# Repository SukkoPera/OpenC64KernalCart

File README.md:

# OpenC64KernalCart
OpenC64KernalCart is an Open Hardware Multi-KERNAL Cartridge for the Commodore 64.

### Summary
This project is derived from an old Turbo DOS V3 cartridge with the help of Jani. It allows replacing the [KERNAL (i.e.: operating system)](https://www.c64-wiki.com/wiki/Kernal) of a Commodore C64 computer with one that is stored on an external cartridge.

OpenC64KernalCart is designed to accept a 64 KB (512 Kilobit) (E)EPROM with a 27512-style pinout. Such chips can hold up to 8 KERNAL images, which can then be selected by jumpers. This makes it very easy to switch among KERNALs at will, without the need of opening the C64 every time. The recommended part is Winbond W27C512 (or W27E512, which is widely available, cheap and electrically erasable, which avoids the need for a clunky UV-eraser. This is the only part that was thoroughly tested. Other parts, even smaller in size, will probably work, but will require an ad-hoc configuration.

The only inconvenience is that you will need to open your C64 once, in order to connect a wire to CPU pin 28 (or wherever you can find the HIRAM signal, grab a multimeter and check for continuity here and there). You will need to connect this wire to the header that is provided on the cartridge for full KERNAL replacement. Note that the cartridge will also appear to work even when this wire is not connected, but that will not allow the external KERNAL to have access to the full RAM range of the C64, which will lead to incompatibilities.

Jani has published [a nice article](http://blog.worldofjani.com/?p=3736) on how we developed this cartridge and how it works in detail, so please refer to it for further information.

### Configuration
**IMPORTANT: ALWAYS TURN YOUR C64 OFF BEFORE MOVING THE CONFIGURATION JUMPERS.**
 
When flashing the contents, make sure that every file is exactly 8192 bytes long and just concatenate them. Then use the following table to set the jumper configuration for your image of choice:

| KERNAL Image # | A13 | A14 | A15 |
|----------------|-----|-----|-----|
| 1              |  L  |  L  |  L  |
| 2              |  H  |  L  |  L  |
| 3              |  L  |  H  |  L  |
| 4              |  H  |  H  |  L  |
| 5              |  L  |  L  |  H  |
| 6              |  H  |  L  |  H  |
| 7              |  L  |  H  |  H  |
| 8              |  H  |  H  |  H  |
 
### License
The OpenC64KernalCart documentation, including the design itself, is copyright &copy; SukkoPera 2019.

OpenC64KernalCart is Open Hardware licensed under the [CERN OHL v. 1.2](http://ohwr.org/cernohl).

You may redistribute and modify this documentation under the terms of the CERN OHL v.1.2. This documentation is distributed *as is* and WITHOUT ANY EXPRESS OR IMPLIED WARRANTIES whatsoever with respect to its functionality, operability or use, including, without limitation, any implied warranties OF MERCHANTABILITY, SATISFACTORY QUALITY, FITNESS FOR A PARTICULAR PURPOSE or infringement. We expressly disclaim any liability whatsoever for any direct, indirect, consequential, incidental or special damages, including, without limitation, lost revenues, lost profits, losses resulting from business interruption or loss of data, regardless of the form of action or legal theory under which the liability may be asserted, even if advised of the possibility or likelihood of such damages.

A copy of the full license is included in file [LICENSE.pdf](LICENSE.pdf), please refer to it for applicable conditions. In order to properly deal with its terms, please see file [LICENSE_HOWTO.pdf](LICENSE_HOWTO.pdf).

The contact points for information about manufactured Products (see section 4.2) are listed in file [PRODUCT.md](PRODUCT.md).

Any modifications made by Licensees (see section 3.4.b) shall be recorded in file [CHANGES.md](CHANGES.md).

The Documentation Location of the original project is https://github.com/SukkoPera/OpenC64KernalCart/.

### Support the Project
Since the project is open you are free to get the PCBs made by your preferred manufacturer, however in case you want to support the development, you can order them from PCBWay through this link:

You get my gratitude and cheap, professionally-made and good quality PCBs, I get some credit that will help with this and [other projects](https://www.pcbway.com/project/member/shareproject/?bmbid=41100). You won't even have to worry about the various PCB options, it's all pre-configured for you!

Also, if you still have to register to that site, [you can use this link](https://www.pcbway.com/setinvite.aspx?inviteid=41100) to get some bonus initial credit (and yield me some more).

Again, if you want to use another manufacturer, feel free to, don't feel obligated :). But then you can buy me a coffee if you want:

### Get Help
If you need help or have questions, you can join [the official Telegram group](https://t.me/joinchat/HUHdWBC9J9JnYIrvTYfZmg).

### Thanks
- Jani for involving me into this project.

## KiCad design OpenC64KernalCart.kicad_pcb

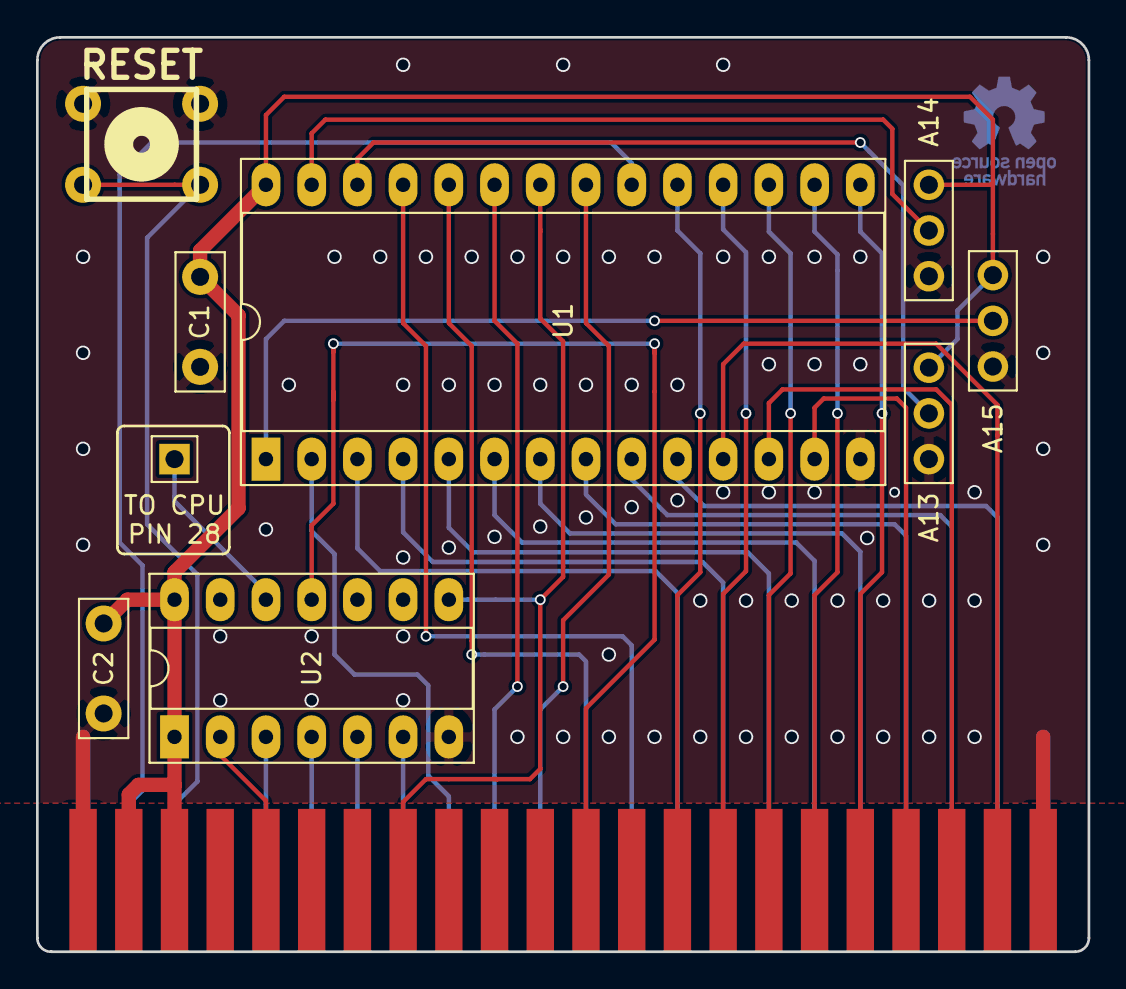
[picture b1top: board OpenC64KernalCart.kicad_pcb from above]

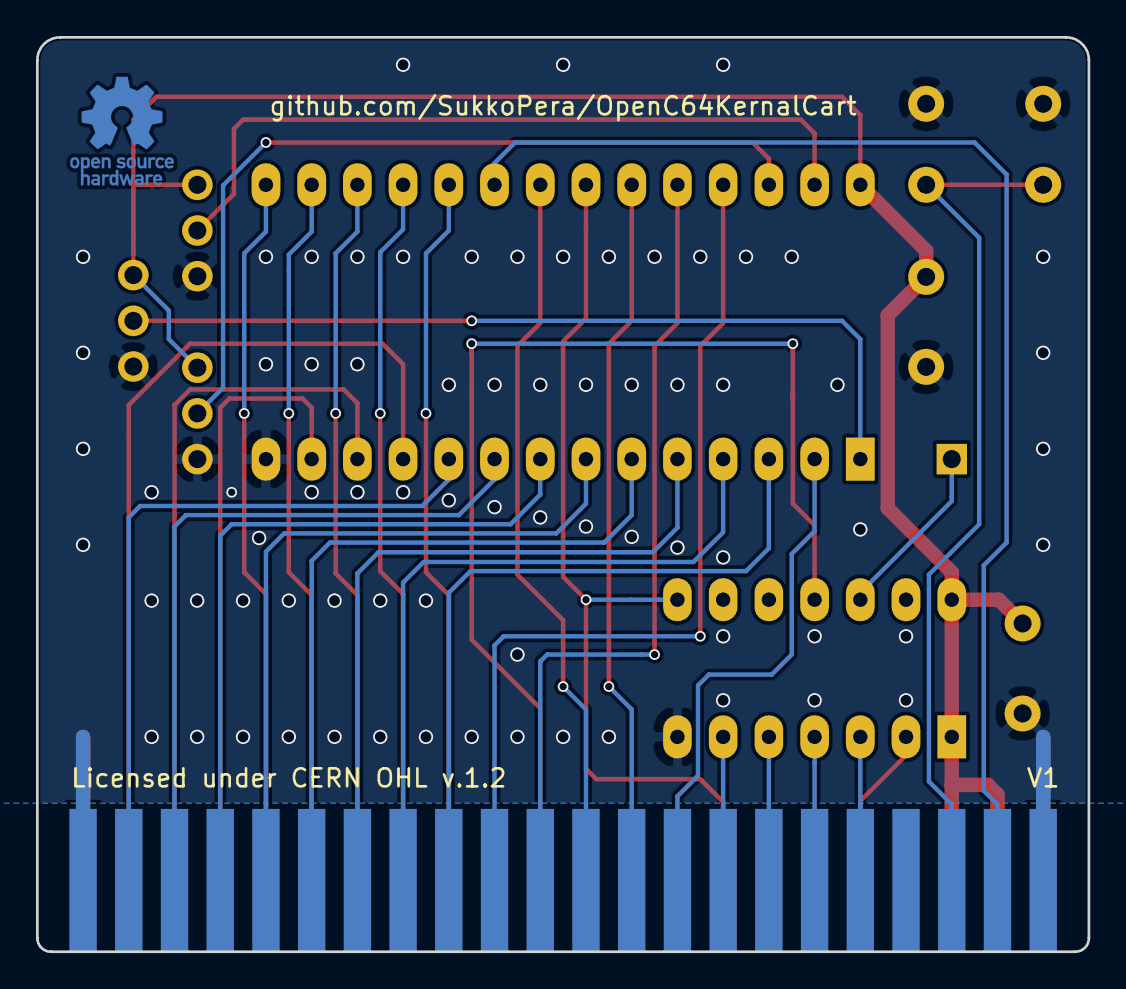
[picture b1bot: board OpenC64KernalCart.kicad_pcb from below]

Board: 2 copper layers, 58.4 x 50.8 mm, 13 parts (2 on the bottom side), 36 nets.

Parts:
C1, C2: 100n; C_Disc_D7.5mm_W2.5mm_P5.00mm
J1: C64-Exp-Port; C64-Cart
J2: CPU_WIRE; PinHeader_1x01_P2.54mm_Vertical
J97: TOP_TRACKS; top
J98: BOTTOM_TRACKS; bottom
J99: OSHW_LOGO; OSHW-Logo_5.7x6mm_Copper
SW2: RESET_SWITCH; PCB_PUSH
SW13: KERNEL_BANK_A13; Switch
SW14: KERNEL_BANK_A14; Switch
SW15: KERNEL_BANK_A15; Switch
U1: 27512; DIP-28_W15.24mm_Socket_LongPads
U2: 74LS30; DIP-14_W7.62mm_Socket_LongPads

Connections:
/a0: J1.Y, U1.10
/a1: J1.X, U1.9
/a2: J1.W, U1.8
/a3: J1.V, U1.7
/a4: J1.U, U1.6
/a5: J1.T, U1.5
/a6: J1.S, U1.4
/a7: J1.R, U1.3
/a8: J1.P, U1.25
/a9: J1.N, U1.24
/a10: J1.M, U1.21
/a11: J1.L, U1.23
/a12: J1.K, U1.2
/a13: J1.J, U2.6
/a13x: SW13.1, U1.26
/a14: J1.H, U2.5
/a14x: SW14.1, U1.27
/a15: J1.F, U2.4
/a15x: SW15.1, U1.1
/ba: J1.12, U2.11
/d0: J1.21, U1.11
/d1: J1.20, U1.12
/d2: J1.19, U1.13
/d3: J1.18, U1.15
/d4: J1.17, U1.16
/d5: J1.16, U1.17
/d6: J1.15, U1.18
/d7: J1.14, U1.19
/game: J1.8, U1.22, U2.8
/phi2: J1.E, U2.3
/reset: J1.C, SW2.1, SW2.2
/romh: J1.B, U1.20
/rw: J1.5, U2.2
/wire: J2.1, U2.12
GND: C1.2, C2.2, J1.1, J1.22, J1.A, J1.Z, SW2.3, SW2.4, SW13.3, SW14.3, SW15.3, U1.14, U2.7
VCC: C1.1, C2.1, J1.2, J1.3, SW13.2, SW14.2, SW15.2, U1.28, U2.1, U2.14

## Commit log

2019-05-20 Initial version, as close as possible as original board
2019-05-21 Sukko's Version 1
2019-05-21 Ready for Sukko's V1
2019-06-26 Some embellishments
2019-07-09 Update images
2019-07-09 Add README and license
2019-07-09 Update fp-info-cache

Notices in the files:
OpenC64KernalCart.kicad_pcb:
Licensed under CERN OHL v.1.2
